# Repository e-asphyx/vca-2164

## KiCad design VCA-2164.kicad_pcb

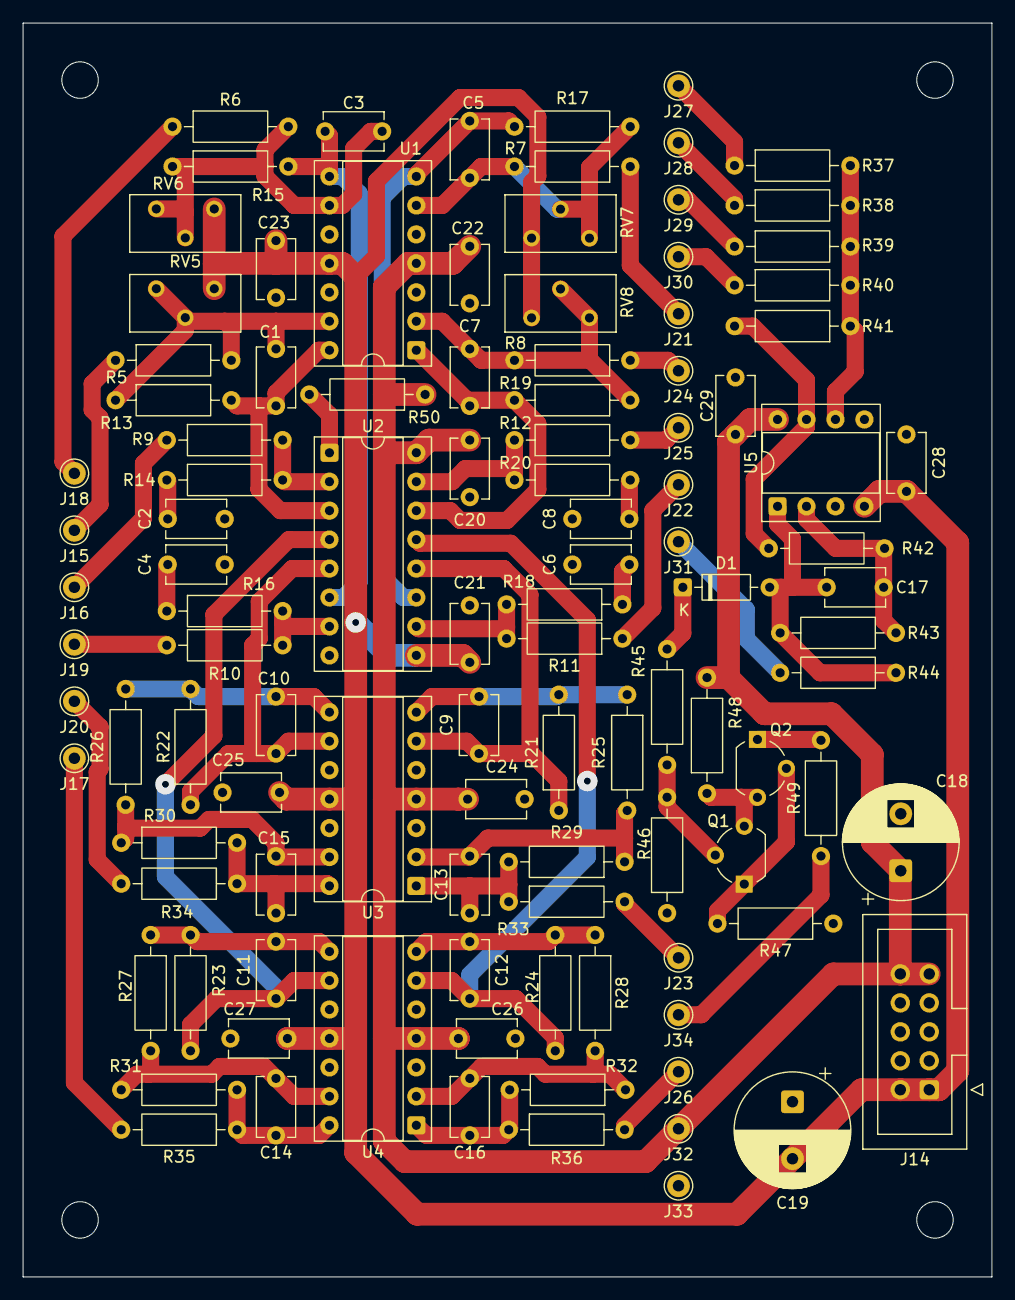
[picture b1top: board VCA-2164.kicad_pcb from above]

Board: 2 copper layers, 85.0 x 110.0 mm, 112 parts (0 on the bottom side), 63 nets.

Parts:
C1, C3, C5, C7, C9, C10, C11, C12: 100p; C_Disc_D5.1mm_W3.2mm_P5.00mm
C2, C4, C6, C8: 560p; C_Disc_D5.1mm_W3.2mm_P5.00mm
C13, C14, C15, C16, C17: 22p; C_Disc_D5.1mm_W3.2mm_P5.00mm
C18, C19: 100u; CP_Radial_D10.0mm_P5.00mm
C20, C21, C22, C23, C24, C25, C26, C27, C28, C29: 0.1u; C_Disc_D5.1mm_W3.2mm_P5.00mm
D1: 1N4148; D_DO-35_SOD27_P7.62mm_Horizontal
H1, H2, H3, H4: MountingHole; MountingHole_3.2mm_M3
J14: Conn_02x05_Odd_Even; IDC-Header_2x05_P2.54mm_Vertical
J15, J16, J17, J18, J19, J20, J21, J22, J23, J24, J25, J26, J27, J28, J29, J30, J31, J32, J33, J34: Conn_01x01; Pin_D1.0mm_L10.0mm
Q1, Q2: BC556; TO-92_Wide
R5, R6, R7, R8, R46: 100k; R_Axial_DIN0207_L6.3mm_D2.5mm_P10.16mm_Horizontal
R9, R10, R11, R12, R21, R22, R23, R24: 33k; R_Axial_DIN0207_L6.3mm_D2.5mm_P10.16mm_Horizontal
R13, R15, R17, R19: 39k; R_Axial_DIN0207_L6.3mm_D2.5mm_P10.16mm_Horizontal
R14, R16, R18, R20: 470; R_Axial_DIN0207_L6.3mm_D2.5mm_P10.16mm_Horizontal
R25, R26, R27, R28, R29, R30, R31, R32, R37, R38, R39, R40, R41, R42, R43, R45: 10k; R_Axial_DIN0207_L6.3mm_D2.5mm_P10.16mm_Horizontal
R33, R34, R35, R36, R44: 1k; R_Axial_DIN0207_L6.3mm_D2.5mm_P10.16mm_Horizontal
R47, R48, R49: 750; R_Axial_DIN0207_L6.3mm_D2.5mm_P10.16mm_Horizontal
R50: 6.8k; R_Axial_DIN0207_L6.3mm_D2.5mm_P10.16mm_Horizontal
RV5, RV6, RV7, RV8: 500k; Potentiometer_Bourns_3296Y_Vertical
U1, U3, U4: TL074; DIP-14_W7.62mm_Socket
U2: AS2164; DIP-16_W7.62mm_Socket
U5: TL072; DIP-8_W7.62mm_Socket

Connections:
/CV_1: J15.1 (Pin_1_1), R5.1
/CV_2: J18.1 (Pin_1_1), R6.1
/CV_3: J21.1 (Pin_1_1), R7.1
/CV_4: J24.1 (Pin_1_1), R8.1
/IN_1: J16.1 (Pin_1_1), R9.1
/IN_2: J19.1 (Pin_1_1), R10.1
/IN_3: J22.1 (Pin_1_1), R11.1
/IN_4: J25.1 (Pin_1_1), R12.1
/LED_A: J34.1 (Pin_1_1), R49.1
/MIX_1: J27.1 (Pin_1_1), R37.1
/MIX_2: J28.1 (Pin_1_1), R38.1
/MIX_3: J29.1 (Pin_1_1), R39.1
/MIX_4: J30.1 (Pin_1_1), R40.1
/MIX_OUT: J31.1 (Pin_1_1), R44.2
/OUT_1: J17.1 (Pin_1_1), R35.2
/OUT_2: J20.1 (Pin_1_1), R34.2
/OUT_3: J23.1 (Pin_1_1), R33.2
/OUT_4: J26.1 (Pin_1_1), R36.2
GND: C2.2, C4.2, C6.2, C8.2, C18.2, C19.1, C20.2, C21.1, C22.2, C23.1, C24.2, C25.1, C26.2, C27.1, C28.1, C29.1, J14.3, J14.4, J14.5, J14.6, J14.7, J14.8, J33.1 (Pin_1_1), R46.1, R47.1, U1.3 (+), U1.5 (+), U1.10 (+), U1.12 (+), U2.8 (GND), U3.3 (+), U3.5 (+), U3.10 (+), U3.12 (+), U4.3 (+), U4.5 (+), U4.10 (+), U4.12 (+), U5.3 (+), U5.5 (+)
unnamed: C1.2, R13.2, U1.14, U2.3
unnamed: C2.1, R14.1
unnamed: C3.2, R15.2, U1.8, U2.6
unnamed: C4.1, R16.1
unnamed: C5.2, R17.2, U1.7, U2.11
unnamed: C6.1, R18.1
unnamed: C7.2, R19.2, U1.1, U2.14
unnamed: C8.1, R20.1
unnamed: C9.2, R21.2, R25.1, U3.7
unnamed: C10.2, R22.2, R26.1, U3.8
unnamed: C11.2, R23.2, R27.1, U4.8
unnamed: C12.2, R24.2, R28.1, U4.7
unnamed: C13.2, R29.2, R33.1, U3.1
unnamed: C14.2, R31.2, R35.1, U4.14
unnamed: C15.2, R30.2, R34.1, U3.14
unnamed: C16.2, R32.2, R36.1, U4.1
unnamed: C17.2, D1.2 (A), R43.2, R44.1, U5.1
unnamed: D1.1 (K), R45.1
unnamed: Q1.2 (B), R45.2, R46.2
unnamed: Q1.1 (C), Q2.2 (B), R47.2
unnamed: Q1.3 (E), Q2.3 (E), R48.1
unnamed: Q2.1 (C), R49.2
unnamed: R10.2, R16.2, U2.7
unnamed: R11.2, R18.2, U2.10
unnamed: R12.2, R20.2, U2.15
unnamed: R9.2, R14.2, U2.2
unnamed: R41.2, R42.1, U5.7
unnamed: C7.1, R8.2, R19.1, RV8.2, RV8.3, U1.2 (-)
unnamed: C5.1, R7.2, R17.1, RV7.2, RV7.3, U1.6 (-)
unnamed: C3.1, R6.2, R15.1, RV6.2, RV6.3, U1.9 (-)
unnamed: C1.1, R5.2, R13.1, RV5.2, RV5.3, U1.13 (-)
unnamed: R50.2, U2.1 (Mode)
unnamed: C13.1, R25.2, R29.1, U3.2 (-)
unnamed: C9.1, R21.1, U2.12, U3.6 (-)
unnamed: C10.1, R22.1, U2.5, U3.9 (-)
unnamed: C15.1, R26.2, R30.1, U3.13 (-)
unnamed: C16.1, R28.2, R32.1, U4.2 (-)
unnamed: C12.1, R24.1, U2.13, U4.6 (-)
unnamed: C11.1, R23.1, U2.4, U4.9 (-)
unnamed: C14.1, R27.2, R31.1, U4.13 (-)
unnamed: C17.1, R42.2, R43.1, U5.2 (-)
unnamed: R37.2, R38.2, R39.2, R40.2, R41.1, U5.6 (-)
VCC: C18.1, C20.1, C22.1, C24.1, C26.1, C29.2, J14.9, J14.10, J32.1 (Pin_1_1), R48.2, R50.1, U1.4 (V+), U2.16 (V+), U3.4 (V+), U4.4 (V+), U5.8 (V+)
VEE: C19.2, C21.2, C23.2, C25.2, C27.2, C28.2, J14.1, J14.2, RV5.1, RV6.1, RV7.1, RV8.1, U1.11 (V-), U2.9 (V-), U3.11 (V-), U4.11 (V-), U5.4 (V-)
